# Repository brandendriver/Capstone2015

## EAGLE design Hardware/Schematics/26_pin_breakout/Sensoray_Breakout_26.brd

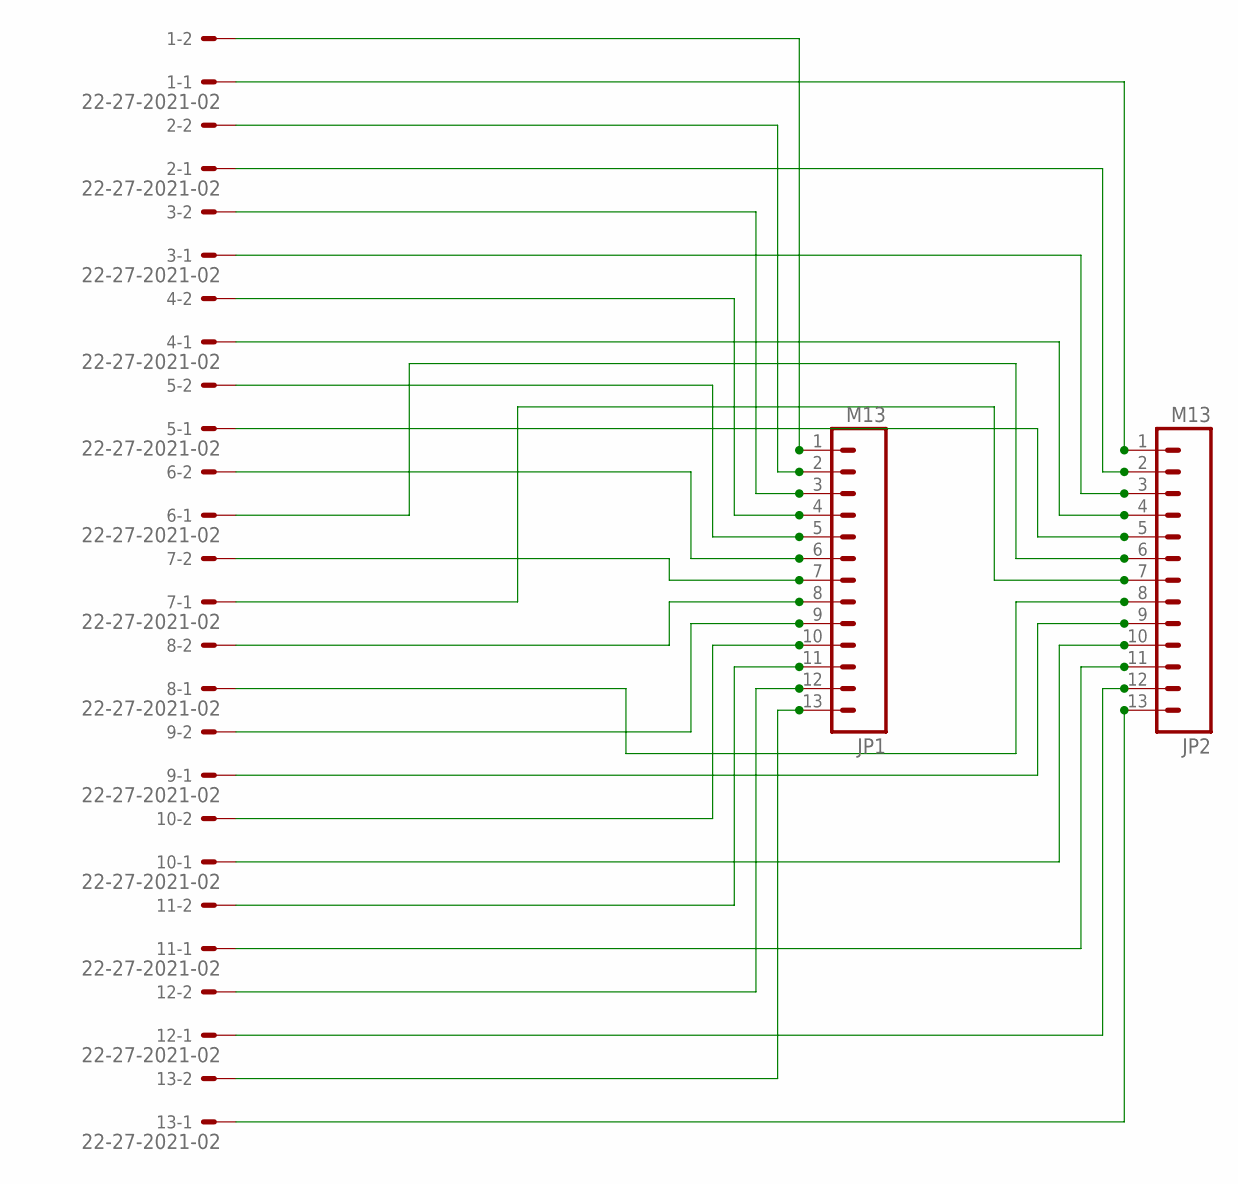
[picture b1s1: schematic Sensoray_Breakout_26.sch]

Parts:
1, 2, 3, 4, 5, 6, 7, 8, 9, 10, 11, 12, 13: 22-27-2021-02; 6410-02
JP1, JP2: M13; 1X13

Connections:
unnamed: 1.2, JP1.1
unnamed: 2.2, JP1.2
unnamed: 3.2, JP1.3
unnamed: 4.2, JP1.4
unnamed: 5.2, JP1.5
unnamed: 6.2, JP1.6
unnamed: 7.2, JP1.7
unnamed: 8.2, JP1.8
unnamed: 9.2, JP1.9
unnamed: 10.2, JP1.10
unnamed: 11.2, JP1.11
unnamed: 12.2, JP1.12
unnamed: 13.2, JP1.13
unnamed: 1.1, JP2.1
unnamed: 2.1, JP2.2
unnamed: 3.1, JP2.3
unnamed: 4.1, JP2.4
unnamed: 5.1, JP2.5
unnamed: 6.1, JP2.6
unnamed: 7.1, JP2.7
unnamed: 13.1, JP2.13
unnamed: 12.1, JP2.12
unnamed: 11.1, JP2.11
unnamed: 10.1, JP2.10
unnamed: 9.1, JP2.9
unnamed: 8.1, JP2.8

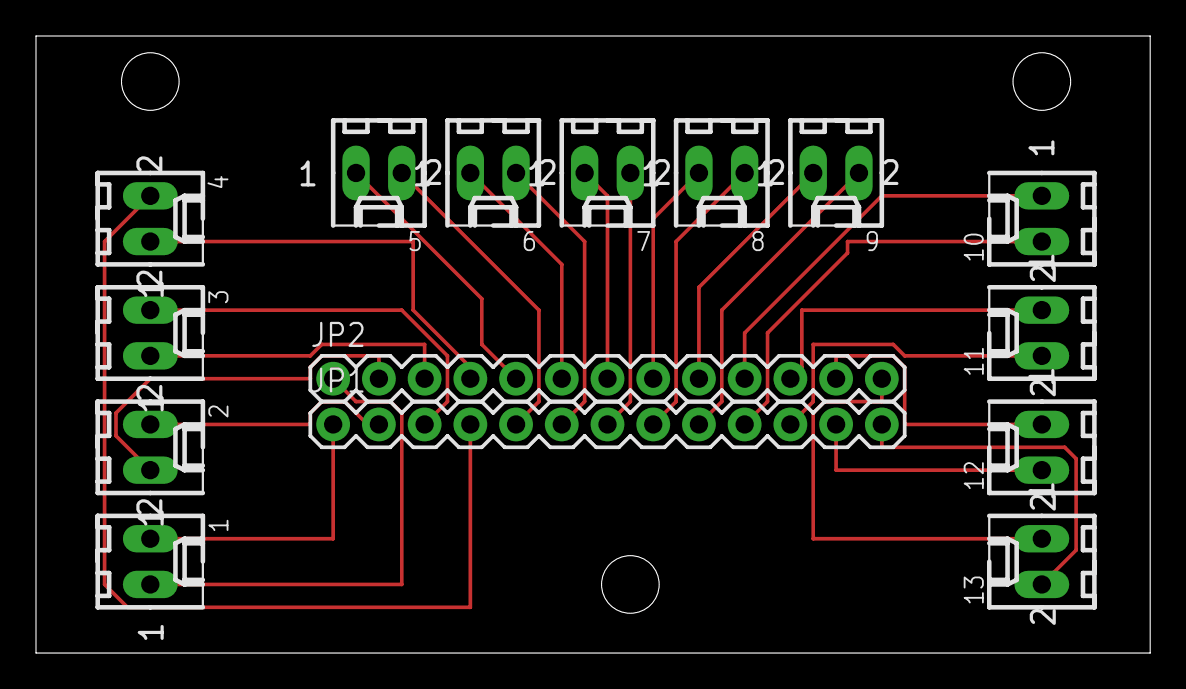
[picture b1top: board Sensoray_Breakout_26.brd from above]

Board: 2 copper layers, 61.9 x 34.3 mm, 15 parts (0 on the bottom side), 26 nets.

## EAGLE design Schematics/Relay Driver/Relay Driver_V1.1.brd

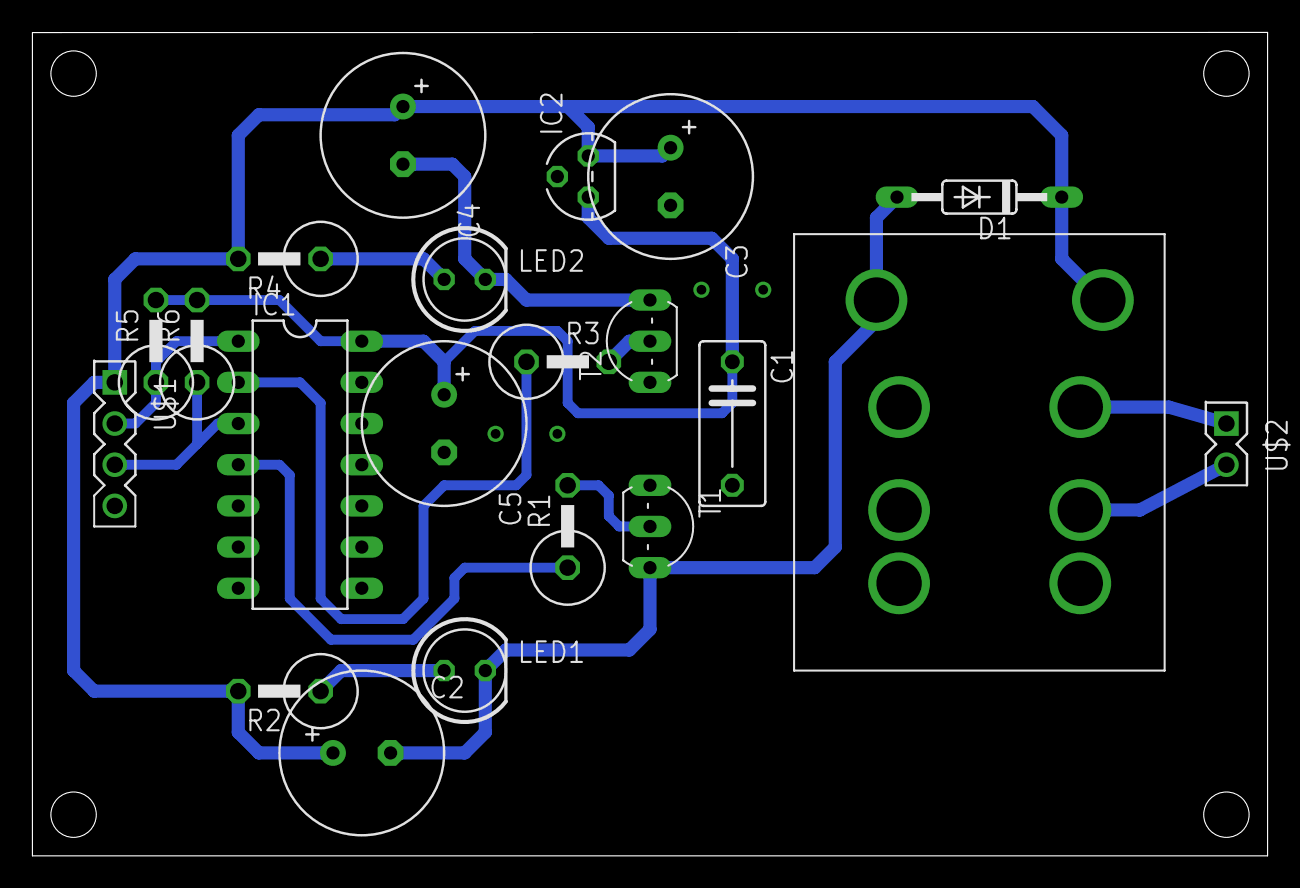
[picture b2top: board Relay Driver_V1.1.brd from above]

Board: 2 copper layers, 76.2 x 50.8 mm, 21 parts (0 on the bottom side), 15 nets.

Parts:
C1: 10nF; C075-042X103
C2, C4: 4.7uF; E3,5-10
C3: .33uF; E3,5-10
C5: 10uF; E3,5-10
D1: 1N4148DO35-10; DO35-10
IC1: 74AC04N; DIL14
IC2: 7805L; TO92
LED1, LED2: LED5MM
R1, R2, R3, R4, R5, R6: 1k; P0613V
RL1: FRL-264
T1, T2: TO92-EBC
U$1: 1X4HEADER_100MIL; 1X4_100MIL
U$2: 1X2HEADER_100MIL; 1X2_100MIL

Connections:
+5V: C1.1, C5.+, IC1.14, IC2.1, R5.2, R6.2
+8V: C2.+, C3.+, C4.+, D1.C, IC2.3, R2.2, R4.2, RL1.COIL+, U$1.1
G0: IC1.2, R3.1
G1: IC1.4, R1.1
GND: C1.2, C3.-, C5.-, IC1.7, IC2.2, T1.E, T2.E, U$1.4
unnamed: R1.2, T1.B
unnamed: RL1.NO1, U$2.2
unnamed: R3.2, T2.B
unnamed: C2.-, D1.A, LED1.K, RL1.COIL-, T1.C
unnamed: RL1.COM1, U$2.1
unnamed: IC1.1, R5.1, U$1.2
unnamed: C4.-, LED2.K, T2.C
unnamed: IC1.3, R6.1, U$1.3
unnamed: LED1.A, R2.1
unnamed: LED2.A, R4.1

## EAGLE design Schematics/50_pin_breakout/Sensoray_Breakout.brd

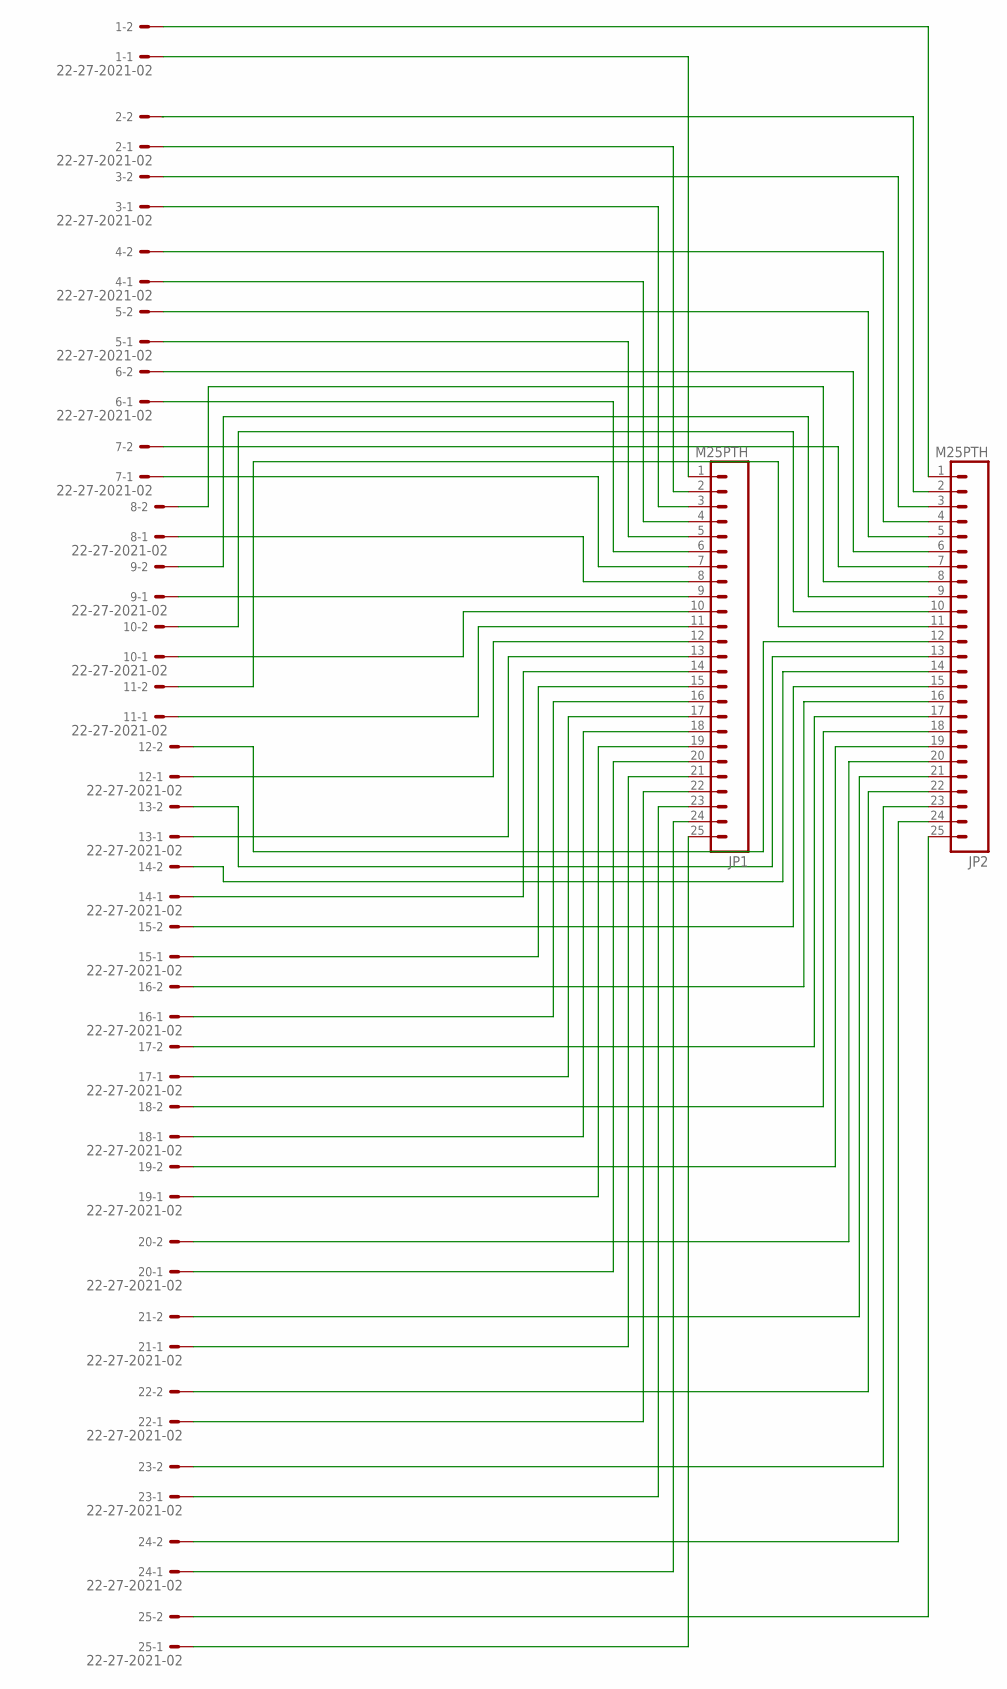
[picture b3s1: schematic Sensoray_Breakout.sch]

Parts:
1, 2, 3, 4, 5, 6, 7, 8, 9, 10, 11, 12, 13, 14, 15, 16, 17, 18, 19, 20, 21, 22, 23, 24, 25: 22-27-2021-02; 6410-02
JP1, JP2: M25PTH; 1X25

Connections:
unnamed: 1.1, JP1.1
unnamed: 2.1, JP1.2
unnamed: 2.2, JP2.2
unnamed: 3.1, JP1.3
unnamed: 4.1, JP1.4
unnamed: 5.1, JP1.5
unnamed: 6.1, JP1.6
unnamed: 7.1, JP1.7
unnamed: 8.1, JP1.8
unnamed: 9.1, JP1.9
unnamed: 25.1, JP1.25
unnamed: 24.1, JP1.24
unnamed: 23.1, JP1.23
unnamed: 22.1, JP1.22
unnamed: 21.1, JP1.21
unnamed: 20.1, JP1.20
unnamed: 19.1, JP1.19
unnamed: 18.1, JP1.18
unnamed: 17.1, JP1.17
unnamed: 16.1, JP1.16
unnamed: 15.1, JP1.15
unnamed: 14.1, JP1.14
unnamed: 13.1, JP1.13
unnamed: 12.1, JP1.12
unnamed: 11.1, JP1.11
unnamed: 10.1, JP1.10
unnamed: 1.2, JP2.1
unnamed: 3.2, JP2.3
unnamed: 4.2, JP2.4
unnamed: 5.2, JP2.5
unnamed: 6.2, JP2.6
unnamed: 7.2, JP2.7
unnamed: 8.2, JP2.8
unnamed: 9.2, JP2.9
unnamed: 10.2, JP2.10
unnamed: 11.2, JP2.11
unnamed: 12.2, JP2.12
unnamed: 13.2, JP2.13
unnamed: 14.2, JP2.14
unnamed: 15.2, JP2.15
unnamed: 16.2, JP2.16
unnamed: 17.2, JP2.17
unnamed: 18.2, JP2.18
unnamed: 19.2, JP2.19
unnamed: 20.2, JP2.20
unnamed: 21.2, JP2.21
unnamed: 22.2, JP2.22
unnamed: 23.2, JP2.23
unnamed: 24.2, JP2.24
unnamed: 25.2, JP2.25

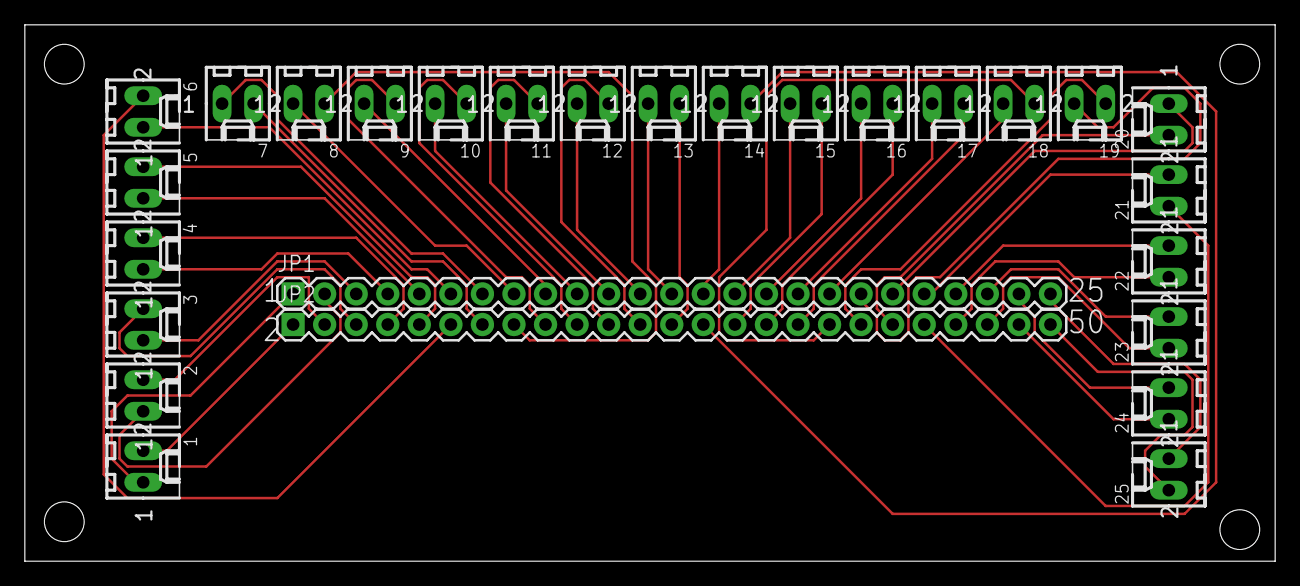
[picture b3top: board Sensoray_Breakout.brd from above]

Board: 2 copper layers, 100.6 x 43.2 mm, 27 parts (0 on the bottom side), 50 nets.

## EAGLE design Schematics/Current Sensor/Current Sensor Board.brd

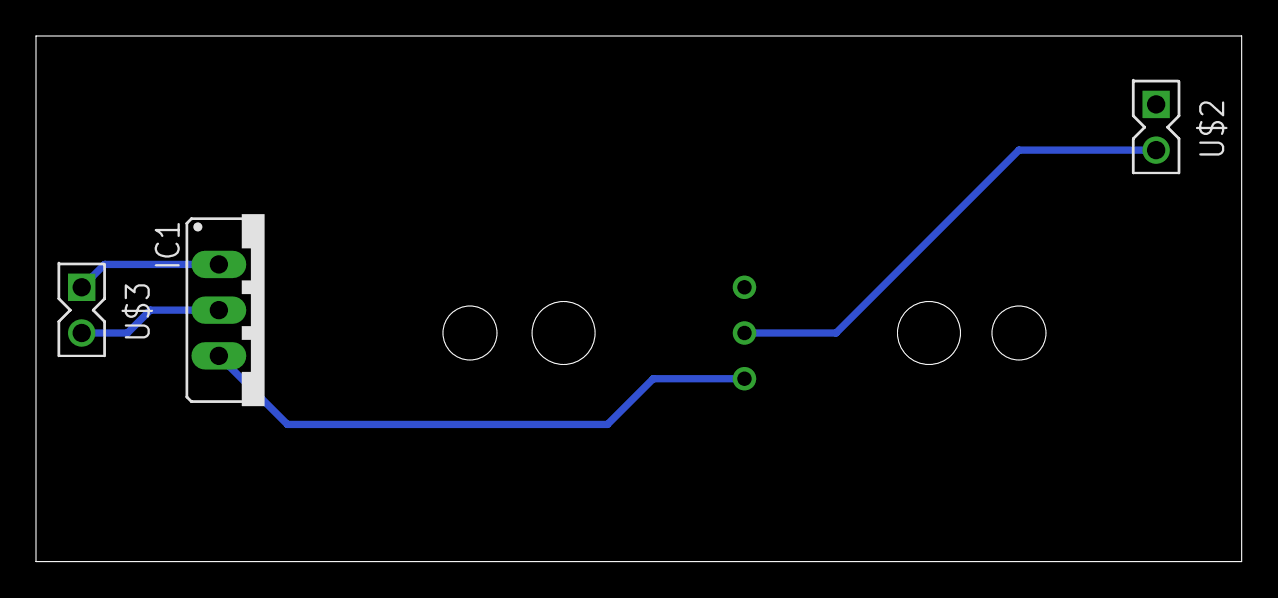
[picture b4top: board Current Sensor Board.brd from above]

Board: 2 copper layers, 67.0 x 29.2 mm, 4 parts (0 on the bottom side), 4 nets.

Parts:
IC1: 78XXS
U$1: CSLA1DJ
U$2, U$3: 1X2HEADER_100MIL; 1X2_100MIL

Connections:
+12V: IC1.OUT, U$1.V+
GND: IC1.GND, U$1.V-, U$2.1, U$3.2
unnamed: IC1.IN, U$3.1
unnamed: U$1.V0, U$2.2

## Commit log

2015-01-20 Created Documentation Folder
    This contains manuals and information for LinuxCNC.
2015-01-21 Added pictures of block diagram from initial meeting with faculty and industry sponsor
2015-01-22 Added Documentation
    Created v1.0 of schedule (word doc) and created title page template to
    bemused with every document
2015-01-22 Updated Documentation
    Created directories for all future WPRs and a template for WPRs
2015-01-23 Added Documentation
    Added WPR for this week, Added app note for temp measurements.
2015-01-23 Added Documentation: WPR Template
2015-01-23 fixing git
2015-01-23 fixing git 1
2015-01-23 Added WPR
2015-01-23 Changed WPR file names
2015-01-23 Added Docuentation
    Created meeting minutes folder and added minutes for 1/23
    Created proposal_v1.0
2015-01-24 Brian added his weekly progress report
2015-01-28 Added Arams thesis and IEEE article
2015-01-28 Proposal Paragraph
2015-01-28 WPR for last week
2015-01-29 adding the presentation, please add your portion and commit it.
2015-01-30 Added Documentation
    Added end goal of project description.
2015-01-30 Updated presentation
2015-02-04 List of controllers/boards ideas
2015-02-04 WPR from last week
2015-02-06 Updated file
2015-02-06 Added Documentation
2015-02-07 Added Documentation
    Sensoray 826 manual
2015-02-10 Update to Board_ideas
2015-02-18 Added documentation and testing
    updated project proposal document and added a new testing document.
2015-02-20 3d testing model
2015-02-21 adding 50-pin breakout schematic
2015-02-22 added 25 pin breakout
2015-02-22 26 pin was mislabelled as 25 pin. corrected this.
2015-03-04 added Rev 2 for 26 and 50 pin breakout boards, along with their gerber files for 1-layer PCB use. also added WPR for week of 27th
2015-03-06 adding v3 of 50 pin board. fixed the pins flipping in the center of the board.
2015-03-30 Added Relay driver schematic
2015-03-30 Added Image
2015-03-30 Added images of breakout boards
2015-03-30 Added Block Diagram Images
2015-03-30 adding current gerber files
2015-03-31 updating progress reports
2015-03-31 added photos of welds
2015-03-31 adding photo of basic GUI Layout idea
2015-03-31 Added Testing documentation
2015-03-31 Added GTK+ part
2015-03-31 Added Gantt Screenshot
2015-04-01 Added Rev 1 for the report
2015-04-01 Added Rev 1
2015-04-01 Updated Documentation
2015-04-01 adding to the progress report
2015-04-01 Deleted old gantt
2015-04-01 Added Combined Gantt Chart
2015-04-01 Added Gantt Chart to the Report
2015-04-02 Updated documentation, added app notes
2015-04-03 Finalized Progress Report
    And moved it to progress report folder.
2015-04-03 Revert "Updated documentation"
    This reverts commit 59a30f0639186ebfaf641f5b771e3c3efc593ec6.
2015-04-03 Test
2015-04-03 test 2
2015-04-03 test 3
2015-04-03 Update documentation
2015-04-03 Added weekly reports
2015-04-03 added
2015-04-03 Updated Progress Report history
2015-04-03 WPR_Qazi
2015-04-03 final 26 pin layout
2015-04-03 minor udpates to progress report
2015-04-03 removing weird temp files that appeared.
2015-04-03 Added Sample Software and BOM
2015-04-03 Added Elaborated GUI Setion
2015-04-03 adding photos from report
2015-04-04 adding WPR
2015-04-05 Added Aram proposal
2015-04-05 Current version of PDF report
2015-04-06 Report V6
2015-04-06 Added G-code description
2015-04-07 Added Report V7
2015-04-08 Added CAD File of Pulley
2015-04-08 Added notes to report.
2015-04-08 Added V8
2015-04-08 Fixed deleted WPRs
2015-04-08 added STL File and updated BOM
2015-04-11 WPR, CAD Files, Current sensor board
    Added my WPR, CAD files for the encoder coupler piece, and the board
    layout and schematic for the current sensor board.
2015-04-14 added berbers for current sensor board and flowchart
    flow chart is for the main control program.
2015-04-15 Adding v1 pseudo code
2015-04-16 Added additional scanned documents
    These include drawings for the encoder mounting, initial control
    flowcharts, and a flowchart for the encoder read program.
2015-04-17 adding a visual studios project file, direct your visual studio to this project folder instead of default. adding preliminary encoder testing code.
2015-04-17 Added How-to for talking to the board
2015-04-17 Added WPRs
2015-04-17 Updating encoder code to V2
2015-04-18 Added data sheets for encoder
2015-04-24 Added manuals to Datasheet and Manual file in Documentation
2015-04-24 updating breakout boards
2015-04-24 updated documentation and scheamtics
    updated current sensor board, and added manual for stepper motor
    controller
2015-04-24 updated hole placement on 26 pin breakout board
2015-04-27 Added new control program software flowchart
2015-04-28 uploading 3d printer v2 pseudo. expanded on the GetCurrent() function and included rough if statements involving drop distances.
2015-04-28 added flowchart for measurements test
2015-04-28 Added Analog Test
2015-04-28 added DIO test and Timer test
2015-04-28 wire speed and droplet spacing near complete pseudo added (maybe v0.8?)
2015-04-29 added code for droplet spacing test
2015-05-01 updated pseudocode
2015-05-01 Added documentation
    Added 1X1X1 test cube STL file, added poster template, added
    calibration testing spreadsheet
2015-05-05 Added Final to do list
2015-05-05 Updated code for measuring droplet spacing
    added algorithm that correctly measures average time between droplet
    spacings by sensing current spikes from welder.
2015-05-05 added code
2015-05-05 added register descriptions
2015-05-08 Added Test Plan folder to Documentation
    Included Wire Speed Test Plan
2015-05-08 Pushed pictures
2015-05-08 Added welding picture
2015-05-08 Added Final Gantt
2015-05-08 Started poster layout
2015-05-08 Added Test Plan template
2015-05-08 Reformatted TP4
2015-05-08 Create gh-pages branch via GitHub
2015-05-08 Fixed Main flo
2015-05-08 Added Report V9
2015-05-08 Added Wire Feed And Droplet Spacing Test REV2
2015-05-08 Added Level-0 Rev2
2015-05-09 Added Level-1 Rev3
2015-05-09 added documentation
    also organized them
2015-05-09 added test results from wire speed test
2015-05-09 Added updated relay driver schematic and board
2015-05-12 Added Gerbers for Relay Driver
2015-05-12 updated berbers for relay driver
2015-05-12 Added picture of block from aram's
2015-05-13 updated relay driver schematic
2015-05-13 Updated BOM
2015-05-14 Added Level-1 Rev4
2015-05-14 Added possible poster text boxes
2015-05-14 Updated WPRs
2015-05-14 adding the main controll program from the control computer.
2015-05-14 Added Reformatted TP1
2015-05-14 Updated poster text doc
2015-05-15 updated calibration table
2015-05-15 Updated all software from controller computer
2015-05-15 Added link to video
2015-05-15 Added Report V10
2015-05-15 Added General Public License to existing code
2015-05-15 updated poster text
2015-05-16 added welder quality test plan
2015-05-16 Added new relay schem image
2015-05-16 updated image
2015-05-17 Updated relay board, updated documentation
2015-05-19 added plans for PWM module case
    also added testing results, more pin assignments, and register
    descriptions
2015-05-20 Added documentation
    added manual for temp sensor, updated pin assignments, updated register
    descriptions,
2015-05-20 Edited the Block Diagrams
2015-05-21 Current Software Push
2015-05-22 added licensing info to all software programs
    also updated poster stuff
2015-05-23 Added V12 of report
2015-05-23 adding function comments to be copied over later
2015-05-23 fixed a space
2015-05-25 adding code comments
2015-05-25 Added documentation
    Major Poster update
2015-05-26 Added pictures
2015-05-27 Organized Repo
2015-05-27 Added "final" version of poster
2015-05-27 Updated Poster
2015-05-27 pictures
2015-05-27 Revert "pictures"
    This reverts commit 19e7fd0e91065d490f92166250ab9b018377cf6b.
2015-05-27 poster update
2015-05-27 new poster update
2015-05-27 created poster pdf
2015-05-27 added poster v2.0
2015-05-27 poster mess up
2015-05-28 adding the current sensor datasheet and v0.8 of the software description
2015-05-29 Added V13 of the report
2015-05-29 New Encoder figure
2015-05-29 Added V14 of the report
2015-06-01 Updated documentation
    Added images of hardware, Hardware description, pin assignments, and BOM
2015-06-02 adding v3 of poster and updating software description
2015-06-03 adding latest code revs from the source computer. Includes GNU.
2015-06-03 updated register descriptions and added comments to 3DP_Controller.c
2015-06-03 Added V15 of Report, updated hardware descriptions, test plans, pin assignments and BOM
2015-06-04 gibberish stuff
2015-06-04 Added picture
2015-06-04 Added hardware pictures
2015-06-04 Updated Documentation
    Added flowcharts and organized repo
2015-06-05 moved software descriptions to software folder
2015-06-05 software description update
    didn't add this one last time
2015-06-05 adadaaaaaaa
2015-06-05 Cleaned up repo
2015-06-05 Added tex folder
2015-06-05 Added hand notes and had calculations
2015-06-05 updated software description
2015-06-05 Added Report V16
2015-06-05 Updated droplet spacing spread sheet
2015-06-05 Kept editing the report
2015-06-05 Added V17 of report, finished BOM, fixed appendix issue
2015-06-09 deleted unused tex files
2015-06-09 removed poster presentation folder
2015-06-09 Updating with Fully commented code
2015-06-09 Updated Report. Named Report_NEW
2015-06-09 updated software description to current.
2015-06-09 Added newest flowchart
2015-06-09 Adding User manual
2015-06-09 changed name of user manual
2015-06-09 Updated report
2015-06-09 Updated Final Report
2015-06-10 adding Gcode and final code from control computer
2015-06-11 Updated final version of report

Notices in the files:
parts and their libraries:
SparkFun-Connectors: Licensing: Creative Commons ShareAlike 4.0 International - https://creativecommons.org/licenses/by-sa/4.0
